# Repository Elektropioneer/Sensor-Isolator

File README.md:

# Sensor-Isolator
Isolating 12V FESTO sensors from 5V MCU with optocouplers.

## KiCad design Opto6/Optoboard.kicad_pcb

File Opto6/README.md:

# Sensor-Isolator
Isolating 12V FESTO sensors from 5V MCU with optocouplers.

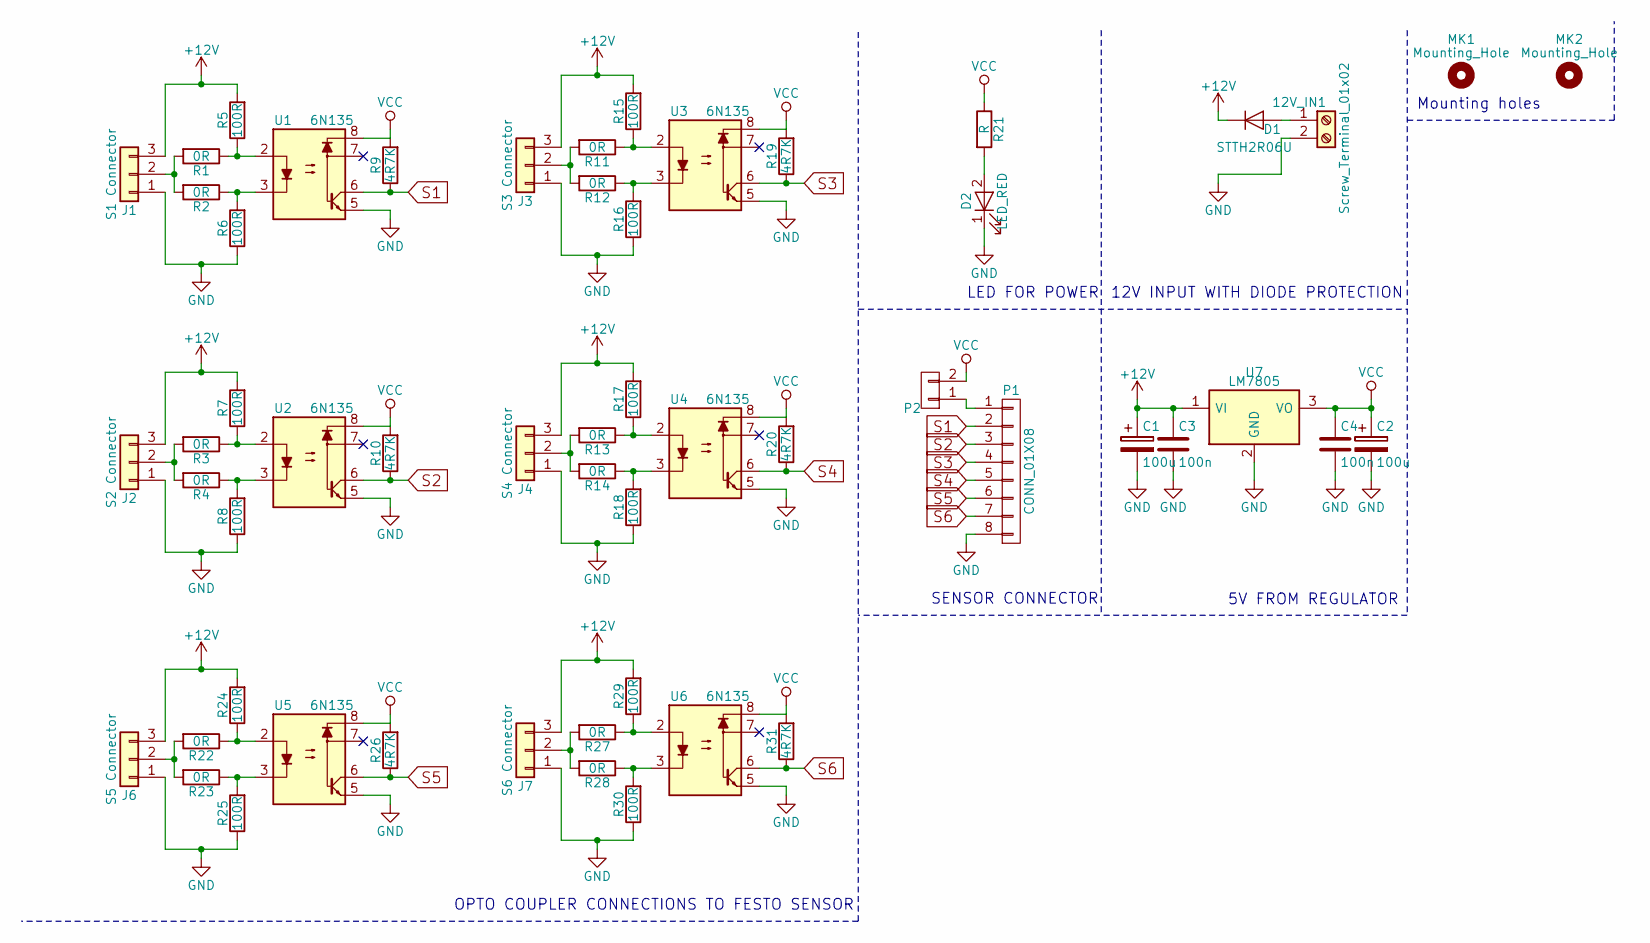
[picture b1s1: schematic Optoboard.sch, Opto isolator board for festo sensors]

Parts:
12V_IN1: Screw_Terminal_01x02; TerminalBlock_Pheonix_MKDS1.5-2pol
C1, C2: 100u; CP_Elec_6.3x5.3
C3, C4: 100n; C_0805
D1: STTH2R06U; D_SMA
D2: LED_RED; LED_1206
J1: S1 Connector; Wafer_Vertical10x5.8x7RM2.5-3
J2: S2 Connector; Wafer_Vertical10x5.8x7RM2.5-3
J3: S3 Connector; Wafer_Vertical10x5.8x7RM2.5-3
J4: S4 Connector; Wafer_Vertical10x5.8x7RM2.5-3
J6: S5 Connector; Wafer_Vertical10x5.8x7RM2.5-3
J7: S6 Connector; Wafer_Vertical10x5.8x7RM2.5-3
MK1, MK2: Mounting_Hole; MountingHole_3.2mm_M3_Pad_Via
P1: CONN_01X08; Pin_Header_Straight_1x08
P2: CONN_01X02; Pin_Header_Straight_1x02
R1, R2, R3, R4, R11, R12, R13, R14, R22, R23, R27, R28: 0R; R_0805
R5, R6, R7, R8, R15, R16, R17, R18, R24, R25, R29, R30: 100R; R_0805
R9, R10, R19, R20, R26, R31: 4R7K; R_0805
R21: R; R_0805
U1, U2, U3, U4, U5, U6: 6N135; DIP-8_W7.62mm
U7: LM7805; TO-252-2Lead

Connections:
+12V: C1.1, C3.1, D1.1 (K), J1.3, J2.3, J3.3, J4.3, J6.3, J7.3, R5.2, R7.2, R15.2, R17.2, R24.2, R29.2, U7.1 (VI)
GND: 12V_IN1.2, C1.2, C2.2, C3.2, C4.2, D2.1 (K), J1.1, J2.1, J3.1, J4.1, J6.1, J7.1, P1.8, R6.1, R8.1, R16.1, R18.1, R25.1, R30.1, U1.5, U2.5, U3.5, U4.5, U5.5, U6.5, U7.2 (GND)
unnamed: 12V_IN1.1, D1.2 (A)
unnamed: D2.2 (A), R21.2
unnamed: J1.2, R1.2, R2.2
unnamed: J2.2, R3.2, R4.2
unnamed: J3.2, R11.2, R12.2
unnamed: J4.2, R13.2, R14.2
unnamed: J6.2, R22.2, R23.2
unnamed: J7.2, R27.2, R28.2
unnamed: P1.1, P2.1
unnamed: R1.1, R5.1, U1.2
unnamed: R2.1, R6.2, U1.3
unnamed: R3.1, R7.1, U2.2
unnamed: R4.1, R8.2, U2.3
unnamed: R11.1, R15.1, U3.2
unnamed: R12.1, R16.2, U3.3
unnamed: R13.1, R17.1, U4.2
unnamed: R14.1, R18.2, U4.3
unnamed: R22.1, R24.1, U5.2
unnamed: R23.1, R25.2, U5.3
unnamed: R27.1, R29.1, U6.2
unnamed: R28.1, R30.2, U6.3
S1: P1.2, R9.1, U1.6
S2: P1.3, R10.1, U2.6
S3: P1.4, R19.1, U3.6
S4: P1.5, R20.1, U4.6
S5: P1.6, R26.1, U5.6
S6: P1.7, R31.1, U6.6
VCC: C2.1, C4.1, P2.2, R9.2, R10.2, R19.2, R20.2, R21.1, R26.2, R31.2, U1.8, U2.8, U3.8, U4.8, U5.8, U6.8, U7.3 (VO)

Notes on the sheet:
OPTO COUPLER CONNECTIONS TO FESTO SENSOR
SENSOR CONNECTOR
5V FROM REGULATOR
LED FOR POWER
12V INPUT WITH DIODE PROTECTION
Mounting holes

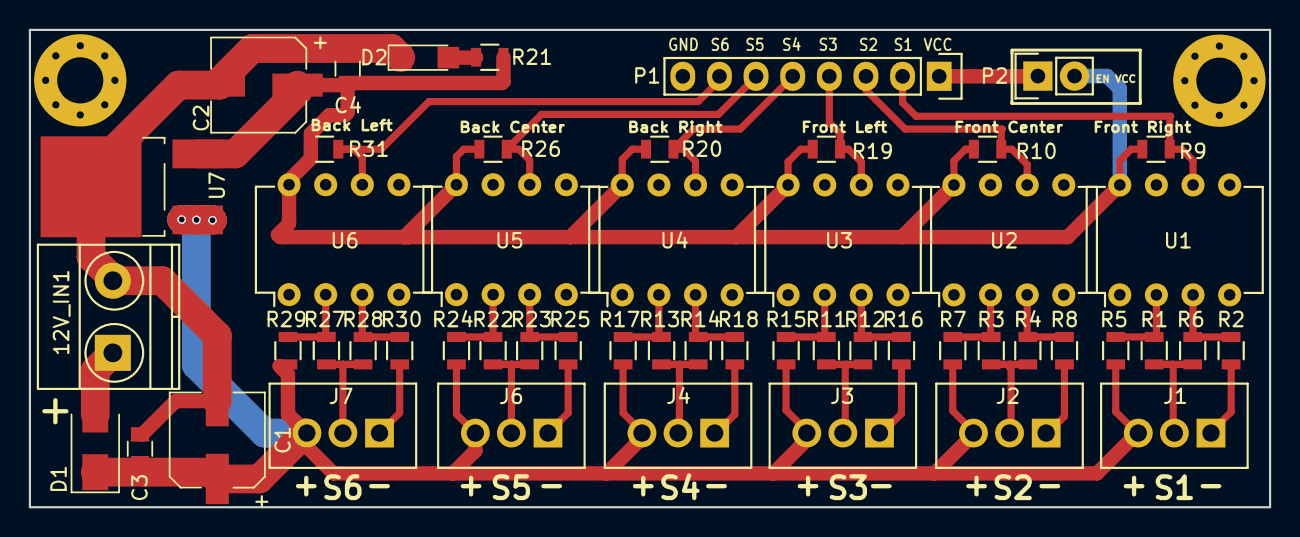
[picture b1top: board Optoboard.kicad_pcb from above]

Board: 2 copper layers, 86.0 x 33.1 mm, 55 parts (0 on the bottom side), 30 nets.

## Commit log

2017-09-25 First commit, everything here needs checkup by reviewer
2017-09-25 Added fancy
2017-09-25 Changed some labels and text
2017-09-30 Changed things that were discussed, also added photos
2017-10-02 Added mounting hole and some writing, 99% ready
2017-10-03 Added hole diameter and moved a label, resistor config coming soon
2017-10-29 Added opto6, images still the same, im tired to screenshot... tomorrow...
2017-10-29 Added opto4 and opto6 updated images
2017-10-30 Changed some traces
2017-10-30 Cleaned up, no more bottom trace, only plain
2017-11-06 Added output files for both version
2017-11-06 Added .cad files
2017-11-06 Added new images
2017-11-08 Added files
2017-11-08 Added output files
2017-11-09 Moved images and readme config
2018-02-10 Modified to 3.3V and 5V compatibility
2018-02-10 Added pdf and images
2018-02-14 Updated the regulator and some small modifs
2018-02-14 Image not loaded....
2018-02-14 Some conflict ...
2018-02-14 Added image, finally?
2018-02-26 Added gerber files
